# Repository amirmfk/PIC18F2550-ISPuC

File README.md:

# PIC18F2550-ISPuC
PIC Microcontroller Development Board Created in KICAD (Schematic and PCB) with Gerber Files

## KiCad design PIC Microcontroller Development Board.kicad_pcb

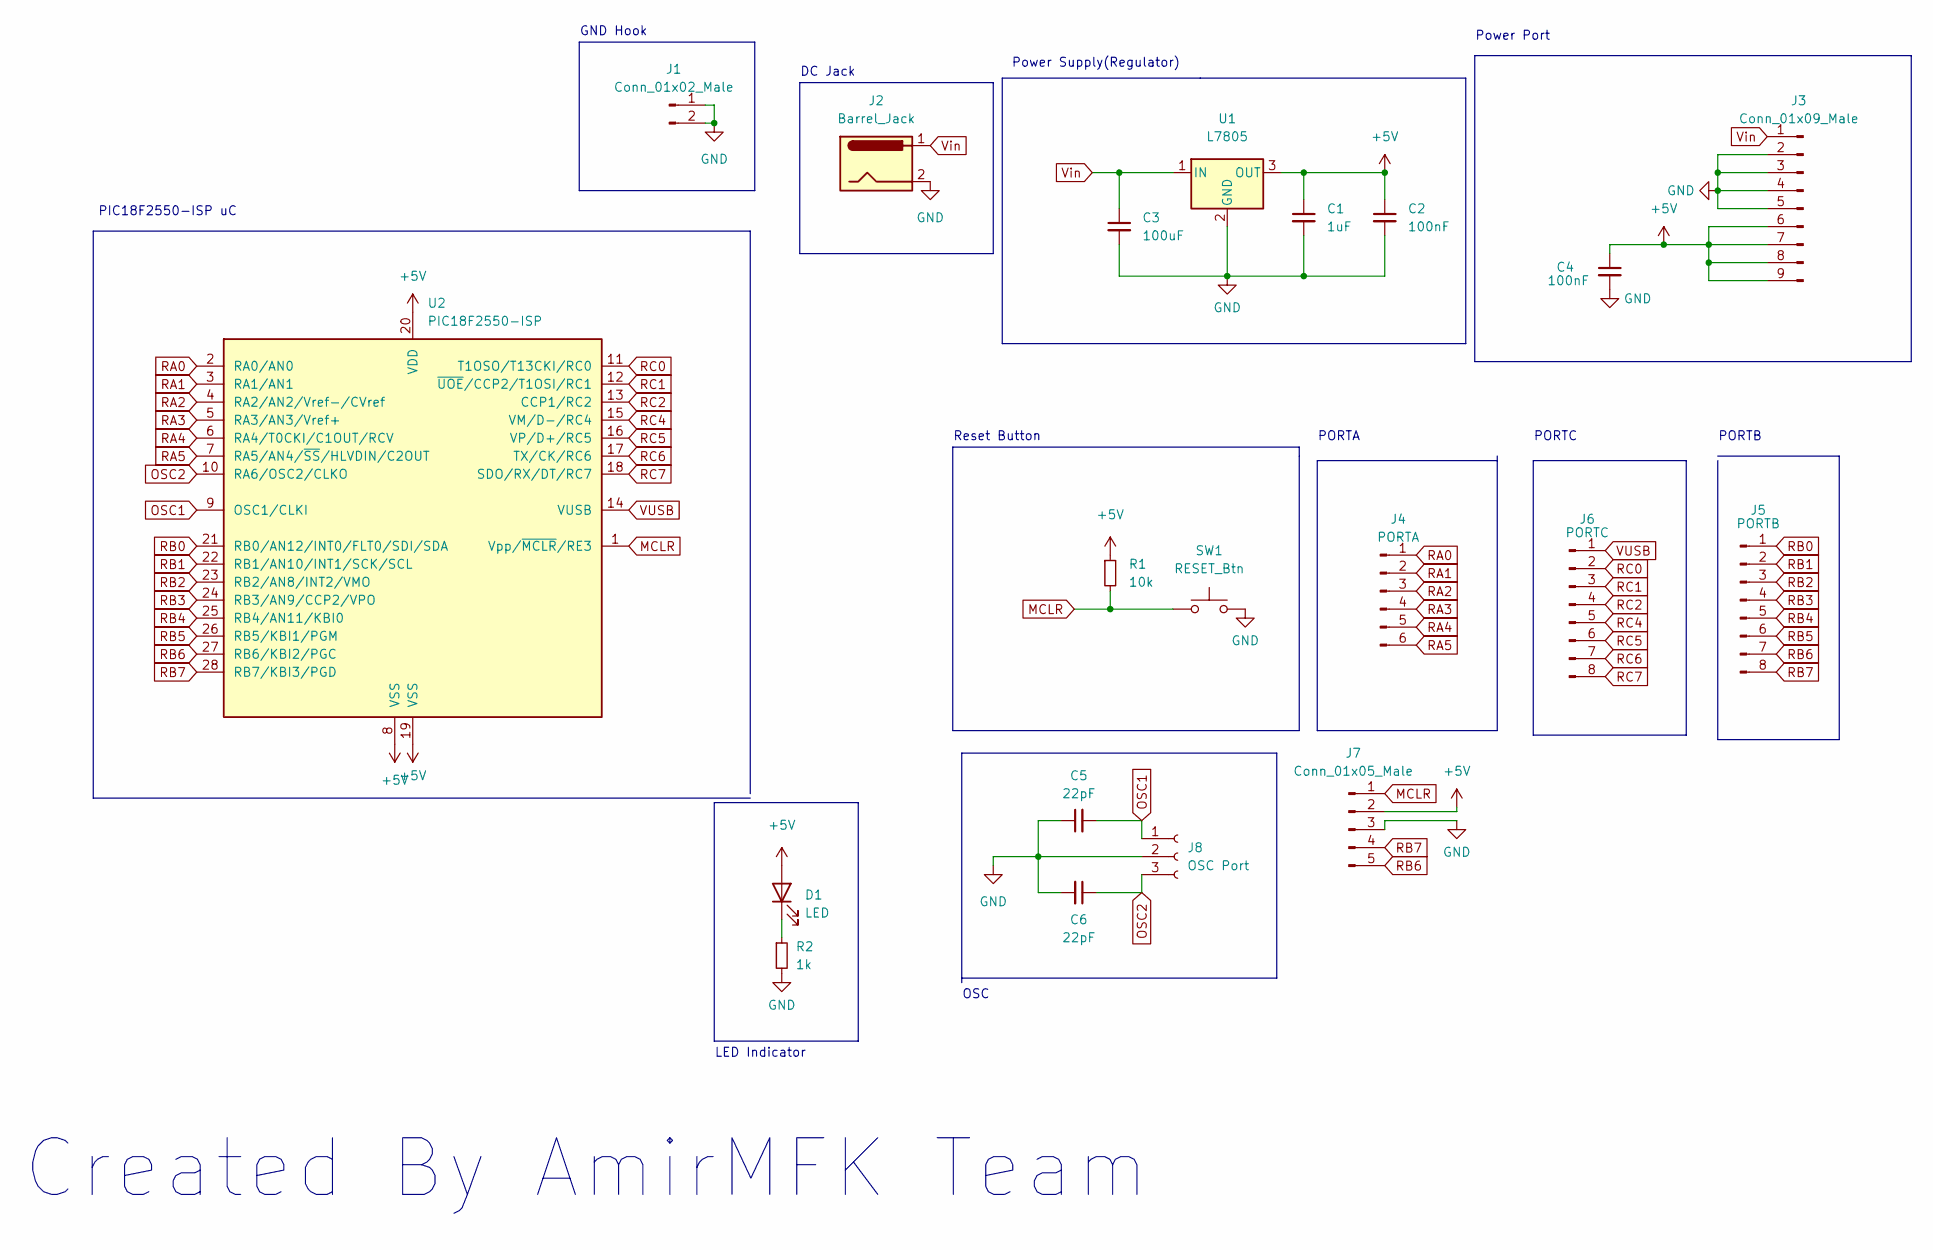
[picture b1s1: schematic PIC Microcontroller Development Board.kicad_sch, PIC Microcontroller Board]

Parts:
C1: 1uF; CP_Radial_D4.0mm_P1.50mm
C2, C4: 100nF; C_Disc_D3.0mm_W1.6mm_P2.50mm
C3: 100uF; CP_Radial_D4.0mm_P2.00mm
C5, C6: 22pF; C_Disc_D3.0mm_W1.6mm_P2.50mm
D1: LED; LED_D3.0mm
J1: Conn_01x02_Male; PinHeader_1x02_P2.54mm_Vertical
J2: Barrel_Jack; BarrelJack_Horizontal
J3: Conn_01x09_Male; PinSocket_1x09_P2.54mm_Vertical
J4: PORTA; PinSocket_1x06_P2.54mm_Vertical
J5: PORTB; PinSocket_1x08_P2.54mm_Vertical
J6: PORTC; PinSocket_1x08_P2.54mm_Vertical
J7: Conn_01x05_Male; PinSocket_1x05_P2.54mm_Vertical
J8: OSC Port; PinSocket_1x03_P2.54mm_Vertical
R1: 10k; R_Axial_DIN0204_L3.6mm_D1.6mm_P5.08mm_Horizontal
R2: 1k; R_Axial_DIN0204_L3.6mm_D1.6mm_P5.08mm_Horizontal
SW1: RESET_Btn; SW_PUSH_6mm
U1: L7805; TO-220-2_Vertical
U2: PIC18F2550-ISP; DIP-28_W7.62mm

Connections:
+5V: C1.1, C2.1, C4.1, D1.2 (A), J3.6, J3.7, J3.8, J3.9, J7.2, R1.1, U1.3 (OUT), U2.8 (VSS), U2.19 (VSS), U2.20 (VDD)
GND: C1.2, C2.2, C3.2, C4.2, C5.1, C6.2, J1.1, J1.2, J2.2, J3.2, J3.3, J3.4, J3.5, J7.3, J8.2, R2.2, SW1.2, U1.2 (GND)
MCLR: J7.1, R1.2, SW1.1, U2.1 (Vpp/~MCLR/RE3)
unnamed: D1.1 (K), R2.1
OSC1: C5.2, J8.1, U2.9 (OSC1/CLKI)
OSC2: C6.1, J8.3, U2.10 (RA6/OSC2/CLKO)
RA0: J4.1, U2.2 (RA0/AN0)
RA1: J4.2, U2.3 (RA1/AN1)
RA2: J4.3, U2.4 (RA2/AN2/Vref-/CVref)
RA3: J4.4, U2.5 (RA3/AN3/Vref+)
RA4: J4.5, U2.6 (RA4/T0CKI/C1OUT/RCV)
RA5: J4.6, U2.7 (RA5/AN4/~SS/HLVDIN/C2OUT)
RB0: J5.1, U2.21 (RB0/AN12/INT0/FLT0/SDI/SDA)
RB1: J5.2, U2.22 (RB1/AN10/INT1/SCK/SCL)
RB2: J5.3, U2.23 (RB2/AN8/INT2/VMO)
RB3: J5.4, U2.24 (RB3/AN9/CCP2/VPO)
RB4: J5.5, U2.25 (RB4/AN11/KBI0)
RB5: J5.6, U2.26 (RB5/KBI1/PGM)
RB6: J5.7, J7.5, U2.27 (RB6/KBI2/PGC)
RB7: J5.8, J7.4, U2.28 (RB7/KBI3/PGD)
RC0: J6.2, U2.11 (T1OSO/T13CKI/RC0)
RC1: J6.3, U2.12 (~UOE/CCP2/T1OSI/RC1)
RC2: J6.4, U2.13 (CCP1/RC2)
RC4: J6.5, U2.15 (VM/D-/RC4)
RC5: J6.6, U2.16 (VP/D+/RC5)
RC6: J6.7, U2.17 (TX/CK/RC6)
RC7: J6.8, U2.18 (SDO/RX/DT/RC7)
VUSB: J6.1, U2.14 (VUSB)
Vin: C3.1, J2.1, J3.1, U1.1 (IN)

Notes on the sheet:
PORTB
Power Port
PIC18F2550-ISP uC
DC Jack
PORTA
GND Hook
Reset Button
Created By AmirMFK Team
PORTC
Power Supply(Regulator)
OSC
LED Indicator

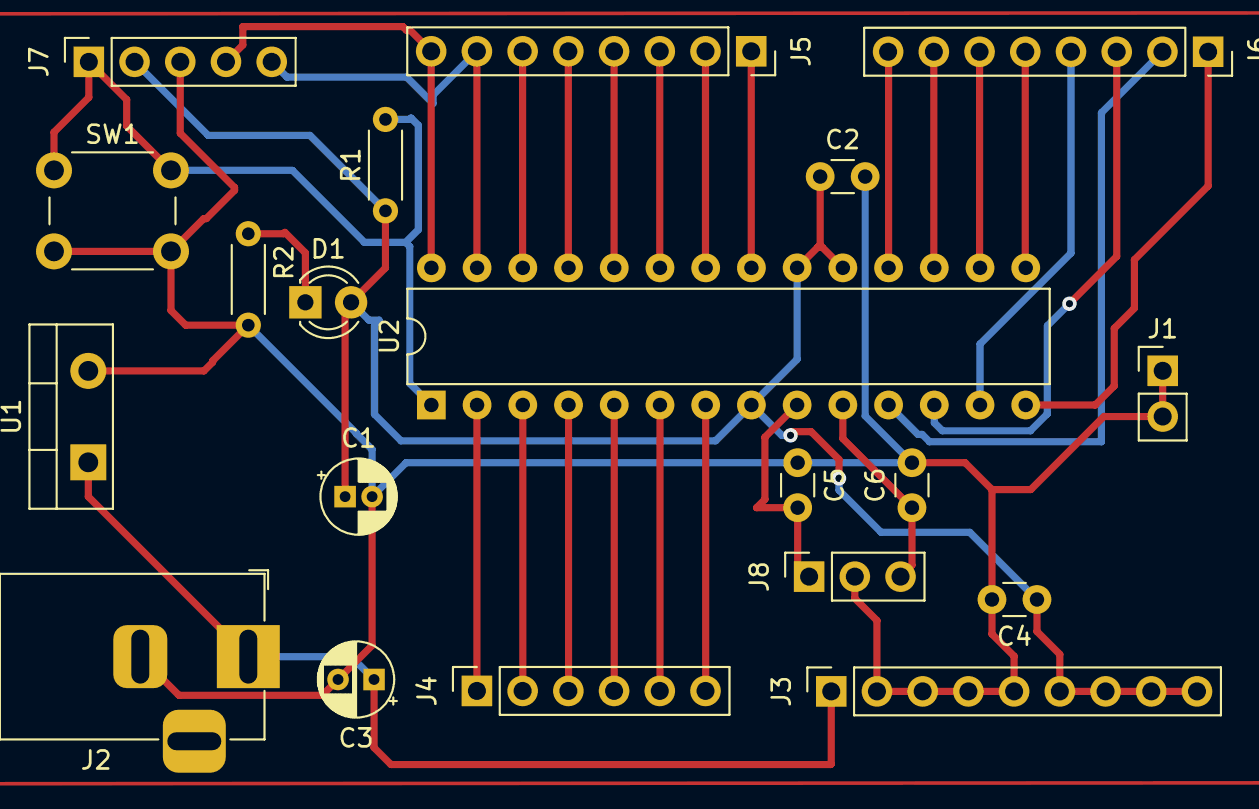
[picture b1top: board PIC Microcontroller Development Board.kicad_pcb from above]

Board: 2 copper layers, 20 parts (0 on the bottom side), 29 nets.

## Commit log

2022-02-10 Add All Files
